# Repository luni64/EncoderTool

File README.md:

# EncoderTool  [![Badge License]][License]  [![Badge Arduino]][Arduino]  [![Badge PlatformIO]][PlatformIO]

*Bounce-Free Rotary Encoder Library* <br>
 **+** *Standard or Multiplexed Wiring* <br>
 **+** *Push Button Support* <br>
 **+** *Callback System*

<br>

<div align = center>

---

[<kbd> <br> Examples <br> </kbd>][Examples] 
[<kbd> <br> Boards <br> </kbd>][Schematics] 
[<kbd> <br> Documentation <br> </kbd>][Documentation] 
[<kbd> <br> Contributors <br> </kbd>][Contributors]

---
</div>

<br>

## Supports

<br>

- All common encoders with and without push buttons

- Directly connected encoders (A+B+Button to pins)

- Multiplexed encoders using

    - [`74HC165 (up to 32 encoders)`][MPLEX74165]

    - [`40HC67  (up to 16 encoders)`][MPLEX4067]

    - [`40HC51  (up to 8 encoders)`][MPLEX4051]
    
    - [`Encoder Matrix`][MPLEX_Matrix]

    - Easy to adapt for your preferred multiplexer

- Interrupt based or polled readout strategies

<br>

## Board Compatibility

<br>

- PJRC Teensy (Teensy-LC, Teensy 3.x, Teensy 4.x, MicroMod)

- SAMD (SEEED XIAO, Nano33 ...)

- 8bit Arduino AVR (UNO, Nano, Mega...)

- ESP32

- Fallback solution for other boards (using slow digitalRead/Write)

<br>

## Features

- Fully bounce free readout without additional hardware

- Provides hard and cyclic count limits

- Supports and debounces encoder push buttons

- Modern callback system for event driven applications

- Encoders can be connected directly (A / B / Btn connected to pins)

- Encoder connection using various multiplexers (up to 32 encoders on only 4 control pins)

- Schematics and Gerbers available for multiplexed encoder boards (Eagle/KiCad).

<!----------------------------------------------------------------------------->

[PlatformIO]: https://registry.platformio.org/libraries/luni64/EncoderTool/
[Arduino]: https://www.arduino.cc/reference/en/libraries/encodertool/

[License]: LICENSE
[MPLEX74165]:Resources/Extras#multiplexing-with-74hc165
[MPLEX4067]:Resources/Extras#multiplexing-with-cd4067
[MPLEX4051]:Resources/Extras#multiplexing-with-cd4051
[MPLEX_Matrix]:Resources/Extras#using-a-directly-connected-encoder-matrix

[Documentation]: Documentation/Overview.md
[Contributors]: Documentation/Contributors.md
[Schematics]: Resources/Extras
[Examples]: examples

[MPLEX74165]: Resources/Extras/Boards/MPX_74165
[MPLEX4067]: Resources/Extras/Boards/MPX_4067
[MPLEX4051]: Resources/Extras/Boards/MPX_4051

<!--------------------------------{ Badges }----------------------------------->

[Badge PlatformIO]: https://img.shields.io/badge/PlatformIO-EncoderTool-fd7e14.svg?style=for-the-badge
[Badge Arduino]: https://img.shields.io/badge/EncoderTool-00979D.svg?style=for-the-badge&logo=Arduino&logoColor=white&labelColor=gray
[Badge License]: https://img.shields.io/badge/License-MIT-yellow.svg?style=for-the-badge

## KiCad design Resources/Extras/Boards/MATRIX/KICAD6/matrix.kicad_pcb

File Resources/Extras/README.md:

# Test Boards

This folder contains proposals and information how to use a 74HC165 shift register or the CD74HC4062 to multiplex rotary encoders. It also contains and a small encoder test board for up to 8 encoders.

<!-- vscode-markdown-toc -->
* [Encoder Board](#EncoderBoard)
* [Multiplexing with 74HC165](#Multiplexerwith74HC165)
* [Multiplexing with CD74HC4067](#MultiplexerwithCD74HC4067)
* [Multiplexing with CD74HC4051](#MultiplexerwithCD74HC4051)
* [Using a directly connected Encoder Matrix](#EncoderMatrix)

<!-- vscode-markdown-toc-config
	numbering=false
	autoSave=true
	/vscode-markdown-toc-config -->
<!-- /vscode-markdown-toc -->

## Encoder Board

Test board for 8 encoders with or without pushbuttons. The layout is done for the common 5mm [footprint](Boards/ENCODER_BOARD/footprint.jpg).

Overview:

- Schematic: [ENC_BOARD_V0.1.pdf](Boards/ENCODER_BOARD/Schematic.pdf)
- Gerbers: [CAMOutputs.zip](Boards/ENCODER_BOARD/Eagle/CAMOutputs.zip)

- BOM: https://octopart.com/bom-tool/XXf3nZh4

Assembly:\

Dimensions:\

## Multiplexing with 74HC165

Multiplexer for 8 encoders with or without additional pushbuttons using two (three) [74HC165](https://octopart.com/search?currency=USD&oq=74HC165+shift&q=74HC165+shift+register&specs=1&case_package=PDIP&case_package=DIP&rohs=Compliant) shift registers.

The following schematic shows the circuit idea. The two phases A and B of up to 8 encoders are connected to the inputs A-H of the first two shift registers. The optional pushbuttons are connected to the inputs of the third shift register.
The controller will use the common clock and load signals to read in the encoders  one after the other. For each encoder it calculates the new encoder count based on the old and the new phases A/B and pushbutton state S. The full schematic of the test board can be found [here](Boards/MPX_74165/MPX_74165_Schematic.pdf).

The board can be daisy chained if you need more than 8 encoders.

### Please note:
The 74HC165 shifts the encoders in from H to A. Thus, if you have less than 8 encoders connect them to H,G...  instead of A,B...

Board:\

Assembly:\

Dimensions:\

- Schematic: [MPX_74165_Schematic.pdf](Boards/MPX_74165/MPX_74165_Schematic.pdf)
- Gerbers: [CAMOutputs.zip](Boards/MPX_74165/Eagle/CAMOutputs.zip)
- BOM: https://octopart.com/bom-tool/vhNEkctc

## Multiplexing with CD4067

The [CD4067](http://www.ti.com/product/CD4067B) is a wide spread and easy to use 16 channel analog/digital multiplexer. Depending on the channel address which has to be supplied at the pins S0-S4, the multiplexer connects one of the 16 inputs C0-C15 to the common output SIG.
To multiplex rotary encoders we use two of the chips, one for the encoder phases A and one for phases B. If you want to use additional pushbuttons you can connect them to an additional multiplexer.

If you don't want to design a dedicated PCB, CD4067 breakout boards are readily available e.g. at SparkFun https://www.sparkfun.com/products/9056.

\
([CC BY 2.0](https://creativecommons.org/licenses/by/2.0/) SparkFun)

The schematic below shows the principle (not all encoders drawn). The pin names are chosen to match the print on the breakout boards.

If you use the breakout boards they can be assembled in the very compact way shown in the drawing below.

![Breakout](Boards/MPX_4067/assembly3d.jpg
)

Extending the assembly to a third board to connect the encoder pushbuttons is straight forward.

## Multiplexing with CD4051

The [CD4051](http://www.ti.com/product/CD4051B) is an 8 channel analog/digital multiplexer, available in through-hole and SMD packages. Depending on the channel address which has to be supplied at the pins S0-S2, the multiplexer connects one of the 8 inputs to the common output.

To multiplex rotary encoders we use two of the chips, one for the encoder phases A and one for phases B. If you want to use additional pushbuttons you can connect them to an additional multiplexer.

The recommended through-hole component is the CD74HC4051. There's an older CD4051B available, but it is too slow to accurately read multiple encoders without significantly slowing down the scanning speed.

The schematic below shows how to connect your encoders and multiplexers ([full PDF](Boards/MPX_4051/MPX_4051_Schematic.pdf)). 3.3V from the Teensy is used to supply VCC.

## Using a directly connected Encoder Matrix

Instead of using external multiplexers one can use a Teensy to read out\
a matrix of encoders.

Here a schematic and 3d views of a corresponding prototype board
([full PDF](Boards/MATRIX/documentation/schematic.pdf)).\
The controller sets one column pin at a time to HIGH and queries\
the A/B/S pins of the individual rows.

The board can be used for prototypes as well as finished products.\
To accommodate the final, mechanical setup the rows and columns\
can be broken apart. Wiring of the singled encoder boards is easy using\
the provided pads. The layout of the board allows to use a Teensy or\
similar board as controller.

Front

Back

Production files (gerbers, drill files) can be found in the extras folder.

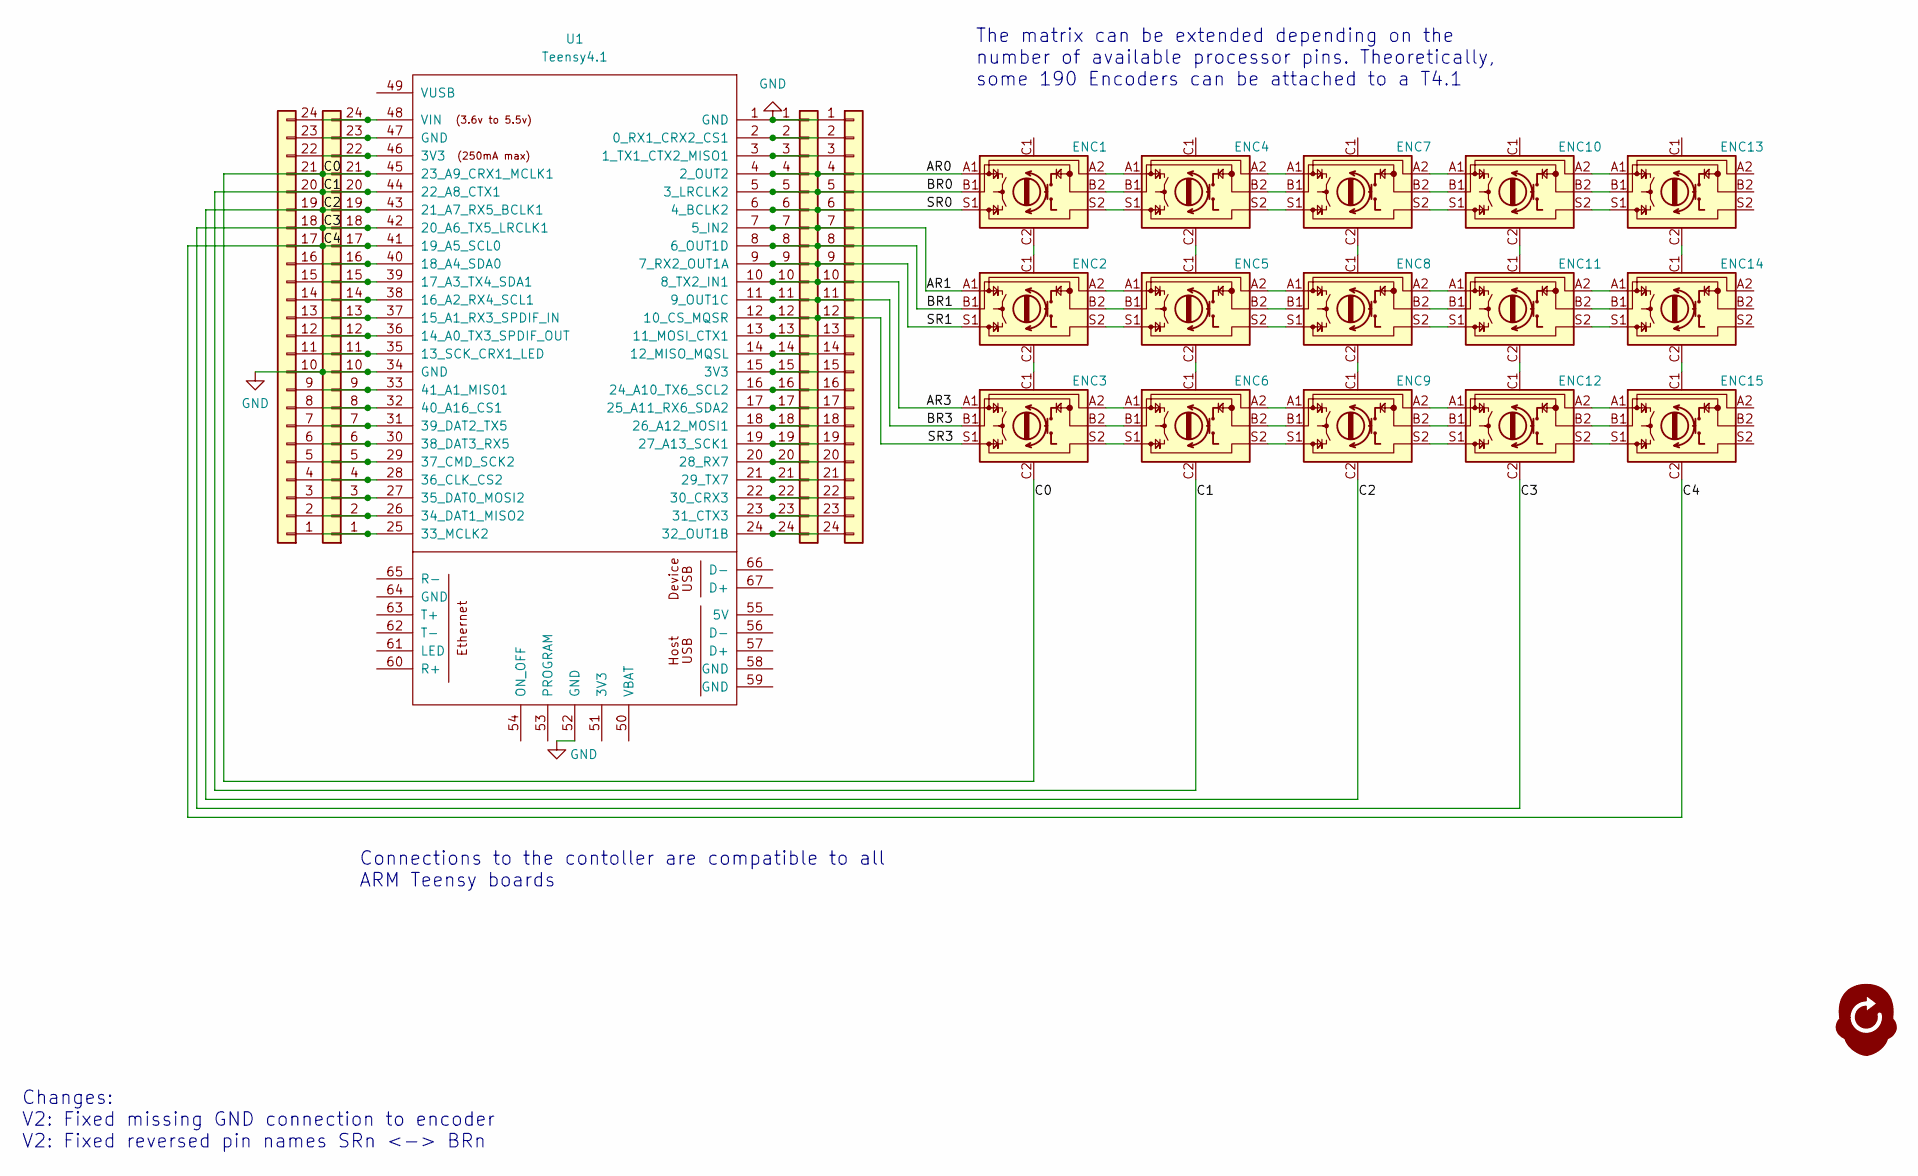
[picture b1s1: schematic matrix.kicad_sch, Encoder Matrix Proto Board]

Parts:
ENC1, ENC2, ENC3, ENC4, ENC5, ENC6, ENC7, ENC8, ENC9, ENC10, ENC11, ENC12, ENC13, ENC14, ENC15: RotaryEncoder_Switch_Matrix; MatrixEncoder EC11
J1, J2, J3, J4: Conn_01x24; PinHeader_1x24_P2.54mm_Vertical
U1: Teensy4.1; Teensy41

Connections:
/AR0: ENC1.A1, J3.4, J4.4, U1.4 (2_OUT2)
/AR1: ENC2.A1, J3.7, J4.7, U1.7 (5_IN2)
/AR3: ENC3.A1, J3.10, J4.10, U1.10 (8_TX2_IN1)
/BR0: ENC1.B1, J3.5, J4.5, U1.5 (3_LRCLK2)
/BR1: ENC2.B1, J3.8, J4.8, U1.8 (6_OUT1D)
/BR3: ENC3.B1, J3.11, J4.11, U1.11 (9_OUT1C)
/C0: ENC3.C2, J1.21, J2.21, U1.45 (23_A9_CRX1_MCLK1)
/C1: ENC6.C2, J1.20, J2.20, U1.44 (22_A8_CTX1)
/C2: ENC9.C2, J1.19, J2.19, U1.43 (21_A7_RX5_BCLK1)
/C3: ENC12.C2, J1.18, J2.18, U1.42 (20_A6_TX5_LRCLK1)
/C4: ENC15.C2, J1.17, J2.17, U1.41 (19_A5_SCL0)
/SR0: ENC1.S1, J3.6, J4.6, U1.6 (4_BCLK2)
/SR1: ENC2.S1, J3.9, J4.9, U1.9 (7_RX2_OUT1A)
/SR3: ENC3.S1, J3.12, J4.12, U1.12 (10_CS_MQSR)
GND: J1.10, J2.10, J3.1, J4.1, U1.1 (GND), U1.34 (GND), U1.52 (GND)
unnamed: ENC1.A2, ENC4.A1
unnamed: ENC1.B2, ENC4.B1
unnamed: ENC1.C2, ENC2.C1
unnamed: ENC1.S2, ENC4.S1
unnamed: ENC2.A2, ENC5.A1
unnamed: ENC2.B2, ENC5.B1
unnamed: ENC2.C2, ENC3.C1
unnamed: ENC2.S2, ENC5.S1
unnamed: ENC3.A2, ENC6.A1
unnamed: ENC3.B2, ENC6.B1
unnamed: ENC3.S2, ENC6.S1
unnamed: ENC4.A2, ENC7.A1
unnamed: ENC4.B2, ENC7.B1
unnamed: ENC4.C2, ENC5.C1
unnamed: ENC4.S2, ENC7.S1
unnamed: ENC5.A2, ENC8.A1
unnamed: ENC5.B2, ENC8.B1
unnamed: ENC5.C2, ENC6.C1
unnamed: ENC5.S2, ENC8.S1
unnamed: ENC6.A2, ENC9.A1
unnamed: ENC6.B2, ENC9.B1
unnamed: ENC6.S2, ENC9.S1
unnamed: ENC7.C2, ENC8.C1
unnamed: ENC8.C2, ENC9.C1
unnamed: ENC7.A2, ENC10.A1
unnamed: ENC10.A2, ENC13.A1
unnamed: ENC7.B2, ENC10.B1
unnamed: ENC10.B2, ENC13.B1
unnamed: ENC10.C2, ENC11.C1
unnamed: ENC7.S2, ENC10.S1
unnamed: ENC10.S2, ENC13.S1
unnamed: ENC8.A2, ENC11.A1
unnamed: ENC11.A2, ENC14.A1
unnamed: ENC8.B2, ENC11.B1
unnamed: ENC11.B2, ENC14.B1
unnamed: ENC11.C2, ENC12.C1
unnamed: ENC8.S2, ENC11.S1
unnamed: ENC11.S2, ENC14.S1
unnamed: ENC9.A2, ENC12.A1
unnamed: ENC12.A2, ENC15.A1
unnamed: ENC9.B2, ENC12.B1
unnamed: ENC12.B2, ENC15.B1
unnamed: ENC9.S2, ENC12.S1
unnamed: ENC12.S2, ENC15.S1
unnamed: ENC13.C2, ENC14.C1
unnamed: ENC14.C2, ENC15.C1
unnamed: J1.1, J2.1, U1.25 (33_MCLK2)
unnamed: J1.2, J2.2, U1.26 (34_DAT1_MISO2)
unnamed: J1.3, J2.3, U1.27 (35_DAT0_MOSI2)
unnamed: J1.4, J2.4, U1.28 (36_CLK_CS2)
unnamed: J1.5, J2.5, U1.29 (37_CMD_SCK2)
unnamed: J1.6, J2.6, U1.30 (38_DAT3_RX5)
unnamed: J1.7, J2.7, U1.31 (39_DAT2_TX5)
unnamed: J1.8, J2.8, U1.32 (40_A16_CS1)
unnamed: J1.9, J2.9, U1.33 (41_A1_MIS01)
unnamed: J1.11, J2.11, U1.35 (13_SCK_CRX1_LED)
unnamed: J1.12, J2.12, U1.36 (14_A0_TX3_SPDIF_OUT)
unnamed: J1.13, J2.13, U1.37 (15_A1_RX3_SPDIF_IN)
unnamed: J1.14, J2.14, U1.38 (16_A2_RX4_SCL1)
unnamed: J1.15, J2.15, U1.39 (17_A3_TX4_SDA1)
unnamed: J1.16, J2.16, U1.40 (18_A4_SDA0)
unnamed: J1.22, J2.22, U1.46 (3V3)
unnamed: J1.23, J2.23, U1.47 (GND)
unnamed: J1.24, J2.24, U1.48 (VIN)
unnamed: J3.2, J4.2, U1.2 (0_RX1_CRX2_CS1)
unnamed: J3.3, J4.3, U1.3 (1_TX1_CTX2_MISO1)
unnamed: J3.13, J4.13, U1.13 (11_MOSI_CTX1)
unnamed: J3.14, J4.14, U1.14 (12_MISO_MQSL)
unnamed: J3.15, J4.15, U1.15 (3V3)
unnamed: J3.16, J4.16, U1.16 (24_A10_TX6_SCL2)
unnamed: J3.17, J4.17, U1.17 (25_A11_RX6_SDA2)
unnamed: J3.18, J4.18, U1.18 (26_A12_MOSI1)
unnamed: J3.19, J4.19, U1.19 (27_A13_SCK1)
unnamed: J3.20, J4.20, U1.20 (28_RX7)
unnamed: J3.21, J4.21, U1.21 (29_TX7)
unnamed: J3.22, J4.22, U1.22 (30_CRX3)
unnamed: J3.23, J4.23, U1.23 (31_CTX3)
unnamed: J3.24, J4.24, U1.24 (32_OUT1B)

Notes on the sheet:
Changes: V2: Fixed missing GND connection to encoder V2: Fixed reversed pin names SRn <-> BRn
Connections to the contoller are compatible to all ARM Teensy boards
The matrix can be extended depending on the number of available processor pins. Theoretically, some 190 Encoders can be attached to a T4.1

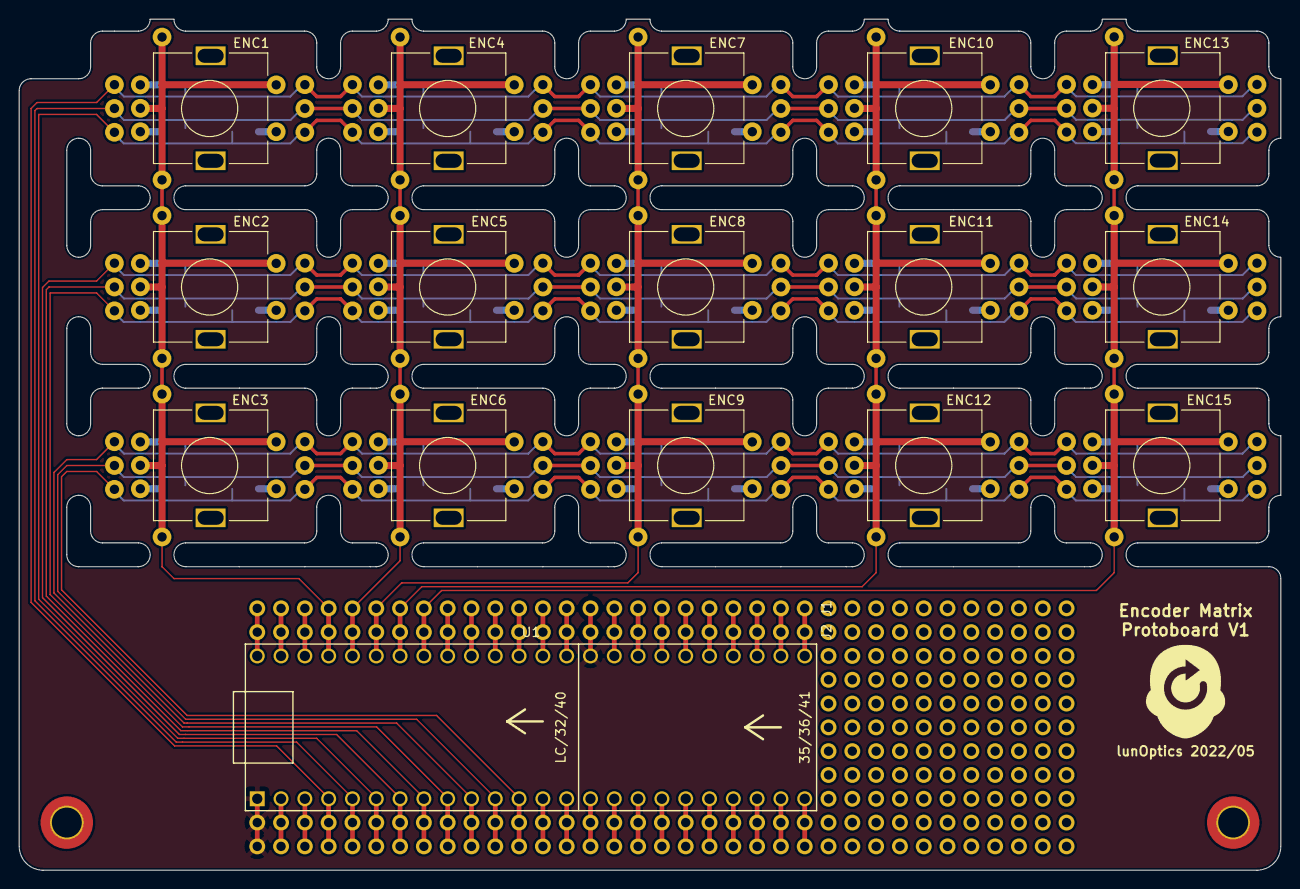
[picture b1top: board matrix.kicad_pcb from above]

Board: 2 copper layers, 134.6 x 90.8 mm, 20 parts (0 on the bottom side), 93 nets.

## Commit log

2020-08-28 updated examples and removed throw_bad_function which is not needed anymore
2020-08-28 Rename setACallback -> attachCallback
2020-08-28 Updated examples
2020-08-28 cleanup
2020-08-29 Bump versions
2020-08-31 Moved count mode to begin instead of constructor
2020-08-31 Added interrupt based single encoder as standard. The polled encoder moved to PolledEncoder class
2020-08-31 Changed the 'all encoders callback' to include delta information to by symmetric to the single encoder callbacks
2020-08-31 Bump version to v2.0.0
2020-09-06 Changed attachInterruptEx to use a more flexible method to generate the relay function array
2020-09-06 cleanup structure
2020-09-06 added button handling in polled and multiplexed encoders
2020-09-06 Encoder button example
2020-09-06 Bump Version
2020-10-04 fixed bug in plain vanilla callbacks
2020-10-04 Switch from std::function to void(*)(Encoder*) for the attached pin interrupts. Reason: avoid a large memory footprint for small MCUs like T-LC
2020-12-02 Update 03_Multiplexed_4067.ino
    Improved call frequency of encoders.tick by eliminating the delay in loop
2020-12-21 workaround std::function issue if _write is not defined. This happens if the linker doesn't link in the print class. Provides a dummy definition for _write
2020-12-23 Fixed wrong conditional code
2020-12-25 Added missing inline declaration
2021-03-07 Added metronome example
2021-03-07 fixed file extension
2021-11-22 Clarified connection of encoders to the 74165 multiplexers
2022-02-10 Add a new class for 4051 multiplexers
    Based on the `EncPlex4067` class, but with three address selector pins instead of 4 and a maximum of 8 encoders.
2022-02-10 Add an example sketch for the 4051
2022-02-10 Add a schematic and documentation for the 4051 multiplexer
2022-02-10 Add 4051 to the readme
2022-02-11 Added 4051 to the TOC
2022-04-24 Fix std::function / printf workaround
    There is a linking issue in Teensyduino which prevents linking in the weak _write function in certain circumstances. The EncoderTool provides a copy of the _write function to avoid this issue.
2022-05-04 Formatted Features
2022-05-04 Added Quicklinks
2022-05-04 Added License Badge
2022-05-04 Added PlatformIO Badge
2022-05-04 Adjusted Style
2022-05-04 Fixed Typo
2022-05-04 Prepare platform independence
2022-05-04 Change digitalWriteFast to HAL::direct read / write
2022-05-04 Prepare platform independent pin interrupts
2022-05-04 Added ESP32 to direct read/write
2022-05-04 Readme experiments
2022-05-04 Copied Over Wiki
2022-05-04 Sorted Files
2022-05-04 Sorted Out Overview
2022-05-04 Updated Links
2022-05-04 Basic Installation Instructions
2022-05-04 Renamed File
2022-05-05 updated badges
2022-05-05 restructured detection of used cores
2022-05-07 Sorted Images
2022-05-07 Formatted Connecting Encoders
2022-05-07 Improve HAL
2022-05-07 Adapted Encoder classes to new HAL
2022-05-07 Formatted Limits
2022-05-08 other readme experiments
2022-05-08 Formatted Interrupts Vs Polling
2022-05-08 Tidied Up Names
2022-05-08 Restructured examples
2022-05-08 Changed encoder values from int32_t to int. -> 16bit for 8bit AVRs, 32bit for ARM processors
2022-05-08 Added the simplyAtomic library to get platform independent ATOMIC blocks.
    Most of the platforms provide atomic ways to set/reset digital pins. For AVR boards this needs to be protected with an atomic block. Same for returning the 16bit counter value
2022-05-08 experiments, to style the readme. Looks like github is removing any css code from the README
2022-05-09 Integrated SimplyAtomic to the repo since platformIO had a hard time autoinstalling it
2022-05-10 fixed dependency bug in library.properties
2022-05-11 Formatted Bouncing
2022-05-11 Added Banners
2022-05-11 Formatted Overview
2022-05-11 Added Button Colors
2022-05-11 Adjusted Spacing
2022-05-11 Fixed Arduino FileSystem
2022-05-11 Formatted Types
2022-05-11 Formatted Guide
2022-05-11 Updated landing page to current state
2022-05-12 Updated Banner
2022-05-12 Formatted Detents
2022-05-12 Fixed Link
2022-05-12 Formatted Reference
2022-05-12 Basic README Fixup
2022-05-13 Added Contributors Page
2022-05-13 Adjusted Filename
2022-05-13 Fixed quick-links formatting
2022-05-15 Squashed commit of the following:
    commit 65bf7239800057a17565193f4fc4afeecebc231b
    Author: luni64 <12611497+luni64@users.noreply.github.com>
    Date: Sun May 15 15:08:58 2022 +0200
    Added MCP23S17 multiplexer example
2022-05-23 Added encoder-matrix board
2022-05-23 Encoder Matrix documentation
2022-05-25 Fixed some platform dependencies in the examples
2022-07-11 Fix directRead for T_LC
2022-07-20 fixed inlining bug preventing linking if lib is included from different translational units
2022-07-20 bump version to v3.03
2022-07-22 Fix directWrite for T_LC
2022-07-22 Bump version to v3.0.5
2022-08-09 matrix example added
2022-08-09 Fixed errors in matrix test board
2022-08-09 bump version to 3.0.6
2022-10-16 User selectable type of the encoder counter
2022-10-17 moved callback typedefs from config.h to base classes to reflect counter type
2022-10-17 Cleaned up API, removed callback from begin function (use attachCallback instead)
2022-10-18 fix wrong type of channel
2022-10-18 Compatibility to 8bit AVR boards (Uno...)
2022-11-29 Merged StaticFunctional, WIP
2022-11-29 Replaced StaticFunctional by the c++ proposed stdext::inplace_function
2022-11-29 Use modern callbacks by default
2022-12-01 Compatibility to c++11 toolchains (WIP)
2022-12-18 Fix examples
2022-12-18 added unit and compile tests
2022-12-18 adapt gitignore to pio project
2023-01-27 Fix namespace issue when using together with TimerTool
2023-02-10 feat: Add button callback to multiplexed
2023-05-24 fix compile issue with non-Teensy boards
2023-10-06 Fixed typo and link to schematic
2023-11-11 Rename to avoid confusion
    This has to be reverted before pullRequest
2023-11-12 isolate update function for btn
2023-11-12 finish allBtnCallback func template
2023-11-12 replicate encoderCallback for button
2023-11-12 Reverted alt dev naming
2024-04-19 Fix wrong startup pin pattern after power on
2025-01-15 first test
2025-08-02 Make error callback work
    ...and enable it
